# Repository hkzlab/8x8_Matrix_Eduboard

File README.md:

# 8x8 LED MATRIX EDUBOARD

## DISCLAIMER

Any use of this project is **under your own responsibility**.
You will be responsible of checking the correct construction and functionality of your board.
By using this project You will agree that I cannot be held responsible if it will destroy any of your devices, damage your computer, burn down your house or whatever.

## Introduction

This board is an educational implementation of an 8x8 multiplexed led matrix. The rows/columns bits can be either addressed via I2C through an MCP23017 or directly through the headers (after unplugging the MCP).

## Features

- Easy to solder through-hole design
- The board works at 3.3V and can be powered from a 4.5V to 8V DC source
- Controlled via i2c on a bog-standard MCP23017 port expander or directly via headers
- Optional onboard pullup resistors for I2C

## Theory of operation

This board is a simple circuit featuring a multiplexed 8x8 LED matrix.

Each column is connected through a resistor to an output of a 74AC244 octal buffer, the inputs of this buffer are controlled either by an MCP23017 port expander or directly by the pins at header J7.

The rows are controlled by a 74HC238 demultiplexer, whose outputs control the base of 8 NPN transistors, each one pulling all the cathodes of the leds on a single row to GND. The '238 demux has 3 inputs, 
piloted by either the MCP expander or directly via the J8 header. Toggling the 3 inputs composes a number in binary ranging from 0 to 7, this number will select which one of the rows will get enabled.
Only one can be active at a time, thus, the demux also acts as a protection avoiding eccessive power consumption if all the columns and leds get enabled together by mistake.

### Pin connections for the MCP23017

| Pin Name | Pin Number | Connection    |
| -------- | ---------- | ------------- |
| GPB0     | 1          | Column 1      |
| GPB1     | 2          | Column 2      |
| GPB2     | 3          | Column 3      |
| GPB3     | 4          | Column 4      |
| GPB4     | 5          | Column 5      |
| GPB5     | 6          | Column 6      |
| GPB6     | 7          | Column 7      |
| GPB7     | 8          | Column 8      |
| GPA5     | 26         | Row Address 2 |
| GPA6     | 27         | Row Address 1 |
| GPA7     | 28         | Row Address 0 |

Notice how the order of the row address lines is reversed in respect to pin numbering. This means that, for example, if you need to enable the fourth row (so row 3, as addressing begins at 0 and ends at 7),
one would need to compose the following binary combination on the pins GPA5-7: `110`, which is the reverse of `011`, or number 3 in decimal.

## Hardware

The board was designed with [KiCad](https://kicad.org/) EDA.

### Bill of Materials

| Component              | Qty | Type / Value                   | Notes                                                    |
| ---------------------- | --- | ------------------------------ | -------------------------------------------------------- |
| C1, C3, C4             |  3  | 100nF multilayer ceramic cap   | 5.0mm pitch                                              |
| C2                     |  1  | 10uF 16V+ electrolytic cap     | 2.5mm pitch                                              |
| D1 - D64               |  64 | Through hole led               | 5.0mm pitch                                              |
| J1, J2, J4, J5, J7, J8 |  1  | snappable 2.5mm pin header     | 20 pins are required for these headers                   |
| J3                     |  1  | snappable 2x3 2.5mm pin header | 6 pins in a 2x3 configuration are required               |
| J6                     |  1  | 1x2 Screw terminal             | 5.0mm pitch, Altech AK300-2 or similar                   |
| Q1 - Q8                |  8  | 2N3904 TO-92 transistors       |                                                          |
| R1 - R8                |  8  | 1K ohm resistors 1/4W          | 1% precision resistors are recommended                   |
| R9 - R16               |  8  | 470 ohm resistors 1/4W         |                                                          |
| R19 - R22              |  4  | 10K ohm resistors              |                                                          |
| R17, R18               |  2  | ~2.2K ohm resistors            | **optional**: install only if I2C pullups are required   |
| RN1                    |  1  | 8x10K ohm bussed resistor array| SIP9 package, bussed configuration                       |
| RN2                    |  1  | 4x10K ohm bussed resistor array| SIP5 package, bussed. a 3x10K SIP4 can be used, leaving last hole empty |
| U1                     |  1  | MCP23017                       | DIP 28 package                                           |
| U2                     |  1  | 74AC245                        | DIP 20 package                                           |
| U3                     |  1  | 74HC238                        | DIP 16 package                                           |
| U4                     |  1  | 78M33 voltage regulator        | TO-220 package                                           |

I strongly recommend to install sockets for all the ICs.

### Fixes

#### Rev. 0

- Rev.0 has a missing power trace. To fix this, join the two pins of header J4 on the underside of the board. A simple drop of solder is enough
- It is recommended to replace D65, the rectifier diode, with a schottky rectifier, like a 1N5818, for lower voltage drop
- Rev.0 lacks pulldown resistors on input pins of the '244 buffer and '238 demultiplexer. It is recommended to add them by soldering a bussed 10K resistor network on the underside of the board, on the solderpoints of headers J7 and J8, scratching the solder mask to access the ground plane for pin 1 of the arrays.

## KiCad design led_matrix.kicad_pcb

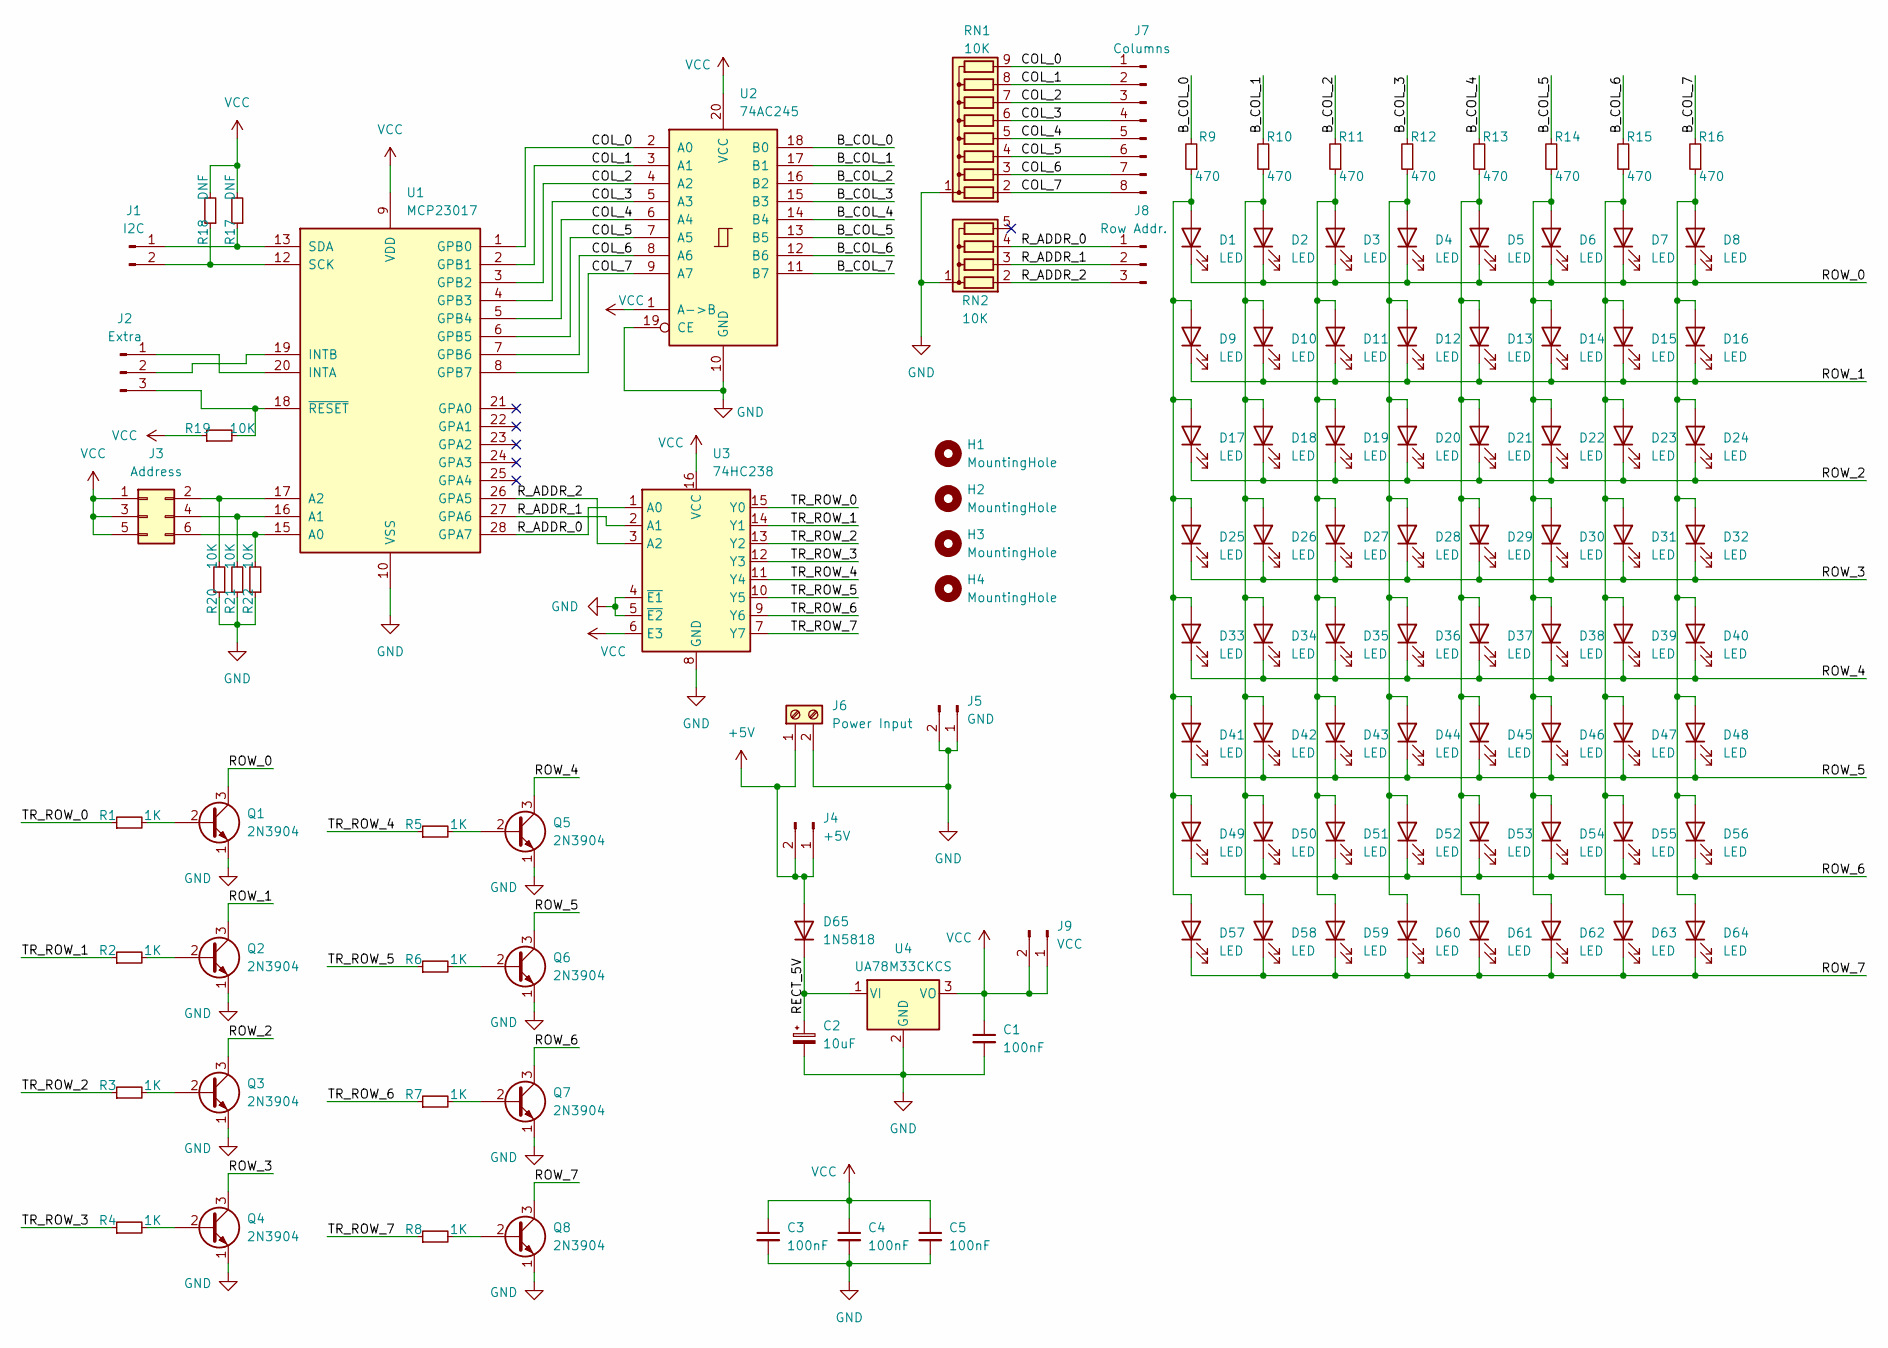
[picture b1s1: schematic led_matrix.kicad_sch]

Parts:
C1, C3, C4, C5: 100nF; C_Disc_D7.0mm_W2.5mm_P5.00mm
C2: 10uF; CP_Radial_D6.3mm_P2.50mm
D1, D2, D3, D4, D5, D6, D7, D8, D9, D10, D11, D12, D13, D14, D15, D16, D17, D18, D19, D20, D21, D22, D23, D24, D25, D26, D27, D28, D29, D30, D31, D32, D33, D34, D35, D36, D37, D38, D39, D40, D41, D42, D43, D44, D45, D46, D47, D48, D49, D50, D51, D52, D53, D54, D55, D56, D57, D58, D59, D60, D61, D62, D63, D64: LED; LED_D5.0mm
D65: 1N5818; D_DO-41_SOD81_P10.16mm_Horizontal
H1, H2, H3, H4: MountingHole; MountingHole_3.5mm
J1: I2C; PinHeader_1x02_P2.54mm_Vertical
J2: Extra; PinHeader_1x03_P2.54mm_Vertical
J3: Address; PinHeader_2x03_P2.54mm_Vertical
J4: +5V; PinHeader_1x02_P2.54mm_Vertical
J5: GND; PinHeader_1x02_P2.54mm_Vertical
J6: Power Input; TerminalBlock_Altech_AK300-2_P5.00mm
J7: Columns; PinHeader_1x08_P2.54mm_Vertical
J8: Row Addr.; PinHeader_1x03_P2.54mm_Vertical
J9: VCC; PinHeader_1x02_P2.54mm_Vertical
Q1, Q2, Q3, Q4, Q5, Q6, Q7, Q8: 2N3904; TO-92_HandSolder
R1, R2, R3, R4, R5, R6, R7, R8: 1K; R_Axial_DIN0207_L6.3mm_D2.5mm_P10.16mm_Horizontal
R9, R10, R11, R12, R13, R14, R15, R16: 470; R_Axial_DIN0207_L6.3mm_D2.5mm_P10.16mm_Horizontal
R17, R18: DNF; R_Axial_DIN0207_L6.3mm_D2.5mm_P10.16mm_Horizontal
R19, R20, R21, R22: 10K; R_Axial_DIN0207_L6.3mm_D2.5mm_P10.16mm_Horizontal
RN1: 10K; R_Array_SIP9
RN2: 10K; R_Array_SIP5
U1: MCP23017; DIP-28_W7.62mm
U2: 74AC245; DIP-20_W7.62mm
U3: 74HC238; DIP-16_W7.62mm
U4: UA78M33CKCS; TO-220-3_Horizontal_TabDown

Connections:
+5V: D65.2 (A), J4.1, J4.2, J6.1
/B_COL_0: R9.2, U2.18 (B0)
/B_COL_1: R10.2, U2.17 (B1)
/B_COL_2: R11.2, U2.16 (B2)
/B_COL_3: R12.2, U2.15 (B3)
/B_COL_4: R13.2, U2.14 (B4)
/B_COL_5: R14.2, U2.13 (B5)
/B_COL_6: R15.2, U2.12 (B6)
/B_COL_7: R16.2, U2.11 (B7)
/COL_0: J7.1, RN1.9 (R8), U1.1 (GPB0), U2.2 (A0)
/COL_1: J7.2, RN1.8 (R7), U1.2 (GPB1), U2.3 (A1)
/COL_2: J7.3, RN1.7 (R6), U1.3 (GPB2), U2.4 (A2)
/COL_3: J7.4, RN1.6 (R5), U1.4 (GPB3), U2.5 (A3)
/COL_4: J7.5, RN1.5 (R4), U1.5 (GPB4), U2.6 (A4)
/COL_5: J7.6, RN1.4 (R3), U1.6 (GPB5), U2.7 (A5)
/COL_6: J7.7, RN1.3 (R2), U1.7 (GPB6), U2.8 (A6)
/COL_7: J7.8, RN1.2 (R1), U1.8 (GPB7), U2.9 (A7)
/RECT_5V: C2.1, D65.1 (K), U4.1 (VI)
/ROW_0: D1.1 (K), D2.1 (K), D3.1 (K), D4.1 (K), D5.1 (K), D6.1 (K), D7.1 (K), D8.1 (K), Q1.3 (C)
/ROW_1: D9.1 (K), D10.1 (K), D11.1 (K), D12.1 (K), D13.1 (K), D14.1 (K), D15.1 (K), D16.1 (K), Q2.3 (C)
/ROW_2: D17.1 (K), D18.1 (K), D19.1 (K), D20.1 (K), D21.1 (K), D22.1 (K), D23.1 (K), D24.1 (K), Q3.3 (C)
/ROW_3: D25.1 (K), D26.1 (K), D27.1 (K), D28.1 (K), D29.1 (K), D30.1 (K), D31.1 (K), D32.1 (K), Q4.3 (C)
/ROW_4: D33.1 (K), D34.1 (K), D35.1 (K), D36.1 (K), D37.1 (K), D38.1 (K), D39.1 (K), D40.1 (K), Q5.3 (C)
/ROW_5: D41.1 (K), D42.1 (K), D43.1 (K), D44.1 (K), D45.1 (K), D46.1 (K), D47.1 (K), D48.1 (K), Q6.3 (C)
/ROW_6: D49.1 (K), D50.1 (K), D51.1 (K), D52.1 (K), D53.1 (K), D54.1 (K), D55.1 (K), D56.1 (K), Q7.3 (C)
/ROW_7: D57.1 (K), D58.1 (K), D59.1 (K), D60.1 (K), D61.1 (K), D62.1 (K), D63.1 (K), D64.1 (K), Q8.3 (C)
/R_ADDR_0: J8.1, RN2.4 (R3), U1.28 (GPA7), U3.1 (A0)
/R_ADDR_1: J8.2, RN2.3 (R2), U1.27 (GPA6), U3.2 (A1)
/R_ADDR_2: J8.3, RN2.2 (R1), U1.26 (GPA5), U3.3 (A2)
/TR_ROW_0: R1.1, U3.15 (Y0)
/TR_ROW_1: R2.1, U3.14 (Y1)
/TR_ROW_2: R3.1, U3.13 (Y2)
/TR_ROW_3: R4.1, U3.12 (Y3)
/TR_ROW_4: R5.1, U3.11 (Y4)
/TR_ROW_5: R6.1, U3.10 (Y5)
/TR_ROW_6: R7.1, U3.9 (Y6)
/TR_ROW_7: R8.1, U3.7 (Y7)
GND: C1.2, C2.2, C3.2, C4.2, C5.2, J5.1, J5.2, J6.2, Q1.1 (E), Q2.1 (E), Q3.1 (E), Q4.1 (E), Q5.1 (E), Q6.1 (E), Q7.1 (E), Q8.1 (E), R20.1, R21.1, R22.1, RN1.1 (common), RN2.1 (common), U1.10 (VSS), U2.10 (GND), U2.19 (CE), U3.4 (~E1), U3.5 (~E2), U3.8 (GND), U4.2 (GND)
unnamed: D1.2 (A), D9.2 (A), D17.2 (A), D25.2 (A), D33.2 (A), D41.2 (A), D49.2 (A), D57.2 (A), R9.1
unnamed: D2.2 (A), D10.2 (A), D18.2 (A), D26.2 (A), D34.2 (A), D42.2 (A), D50.2 (A), D58.2 (A), R10.1
unnamed: D3.2 (A), D11.2 (A), D19.2 (A), D27.2 (A), D35.2 (A), D43.2 (A), D51.2 (A), D59.2 (A), R11.1
unnamed: D4.2 (A), D12.2 (A), D20.2 (A), D28.2 (A), D36.2 (A), D44.2 (A), D52.2 (A), D60.2 (A), R12.1
unnamed: D5.2 (A), D13.2 (A), D21.2 (A), D29.2 (A), D37.2 (A), D45.2 (A), D53.2 (A), D61.2 (A), R13.1
unnamed: D6.2 (A), D14.2 (A), D22.2 (A), D30.2 (A), D38.2 (A), D46.2 (A), D54.2 (A), D62.2 (A), R14.1
unnamed: D7.2 (A), D15.2 (A), D23.2 (A), D31.2 (A), D39.2 (A), D47.2 (A), D55.2 (A), D63.2 (A), R15.1
unnamed: D8.2 (A), D16.2 (A), D24.2 (A), D32.2 (A), D40.2 (A), D48.2 (A), D56.2 (A), D64.2 (A), R16.1
unnamed: J1.1, R17.1, U1.13 (SDA)
unnamed: J1.2, R18.1, U1.12 (SCK)
unnamed: J2.1, U1.20 (INTA)
unnamed: J2.2, U1.19 (INTB)
unnamed: J2.3, R19.2, U1.18 (~RESET)
unnamed: J3.2, R20.2, U1.17 (A2)
unnamed: J3.4, R21.2, U1.16 (A1)
unnamed: J3.6, R22.2, U1.15 (A0)
unnamed: Q1.2 (B), R1.2
unnamed: Q2.2 (B), R2.2
unnamed: Q3.2 (B), R3.2
unnamed: Q4.2 (B), R4.2
unnamed: Q5.2 (B), R5.2
unnamed: Q6.2 (B), R6.2
unnamed: Q7.2 (B), R7.2
unnamed: Q8.2 (B), R8.2
VCC: C1.1, C3.1, C4.1, C5.1, J3.1, J3.3, J3.5, J9.1, J9.2, R17.2, R18.2, R19.1, U1.9 (VDD), U2.1 (A->B), U2.20 (VCC), U3.6 (E3), U3.16 (VCC), U4.3 (VO)

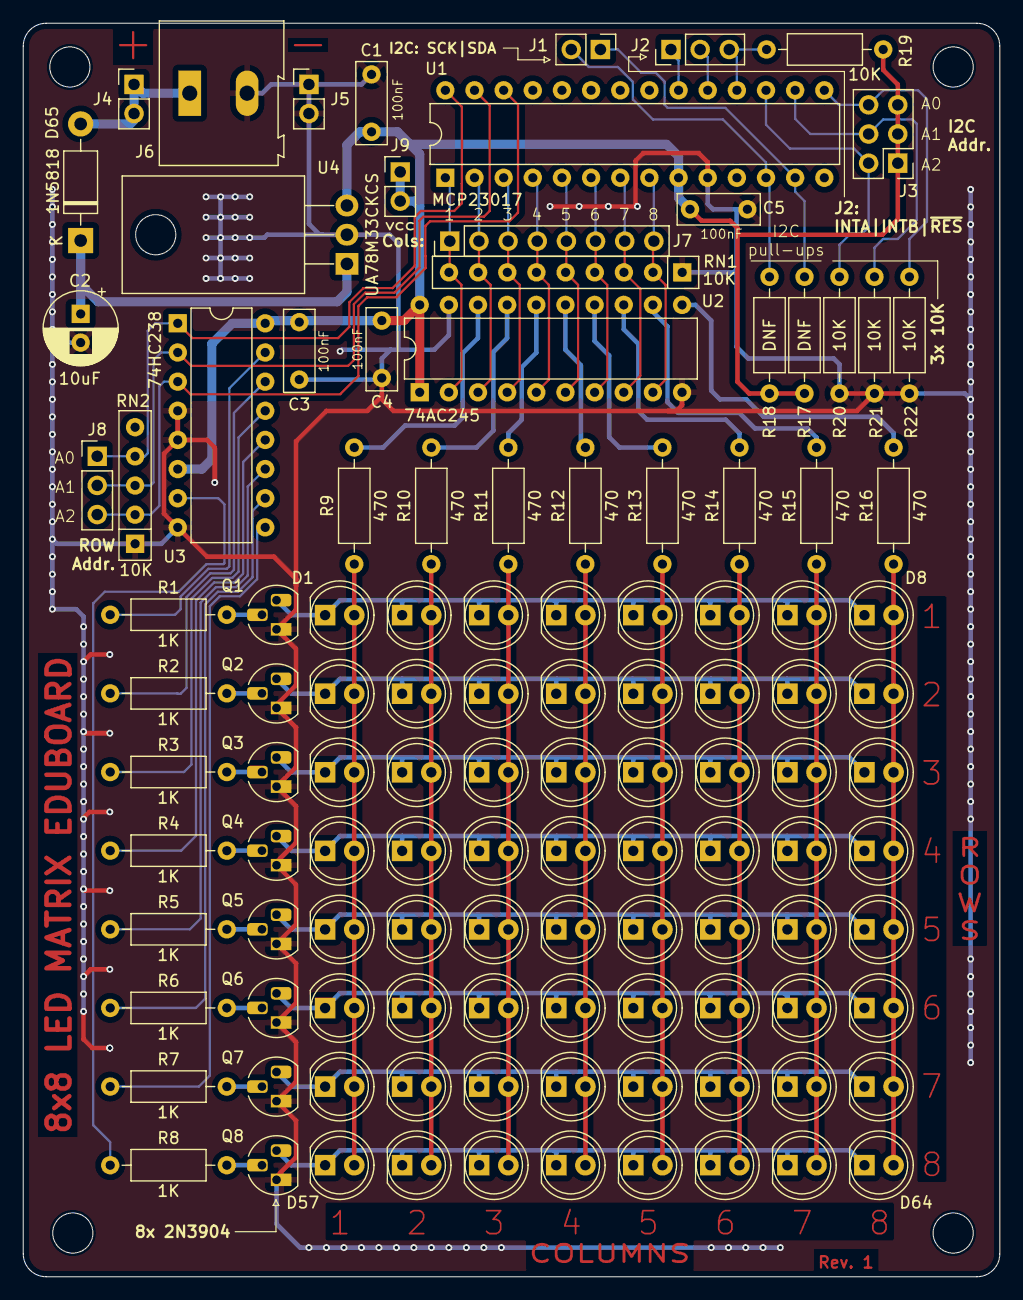
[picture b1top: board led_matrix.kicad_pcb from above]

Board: 2 copper layers, 85.1 x 109.2 mm, 119 parts (0 on the bottom side), 63 nets.

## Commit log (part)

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2024-11-09 First schematic
2024-11-09 Add holes and caps
2024-11-10 Update project
2024-11-11 Update silkscreen
2024-11-12 Update PCB
2024-11-21 Update silkscreen a bit
2024-11-21 Further silkscreen updates
2024-11-21 Update board organization, silkscreen and power regulator placement
2024-11-21 Updated the silkscreen
2024-11-21 Further adjustments to silkscreen
2024-11-21 Update the silkcreen and solder mask
2024-11-21 reorganize some traces
2024-11-21 Enlarge mounting holes
2024-11-23 Reorganized some traces
2024-11-27 Update the gerbers for this board, reorganized some text
2024-12-14 Fix missing 5V connection between two points of an header
2024-12-14 Added an header to pick VCC after the regulator
2024-12-15 Add pulldown resistors to schematic for input pins
2024-12-15 Replace diode type with a schottky one
2024-12-15 Added resistor networks on PCB
2024-12-15 Moved around some components
